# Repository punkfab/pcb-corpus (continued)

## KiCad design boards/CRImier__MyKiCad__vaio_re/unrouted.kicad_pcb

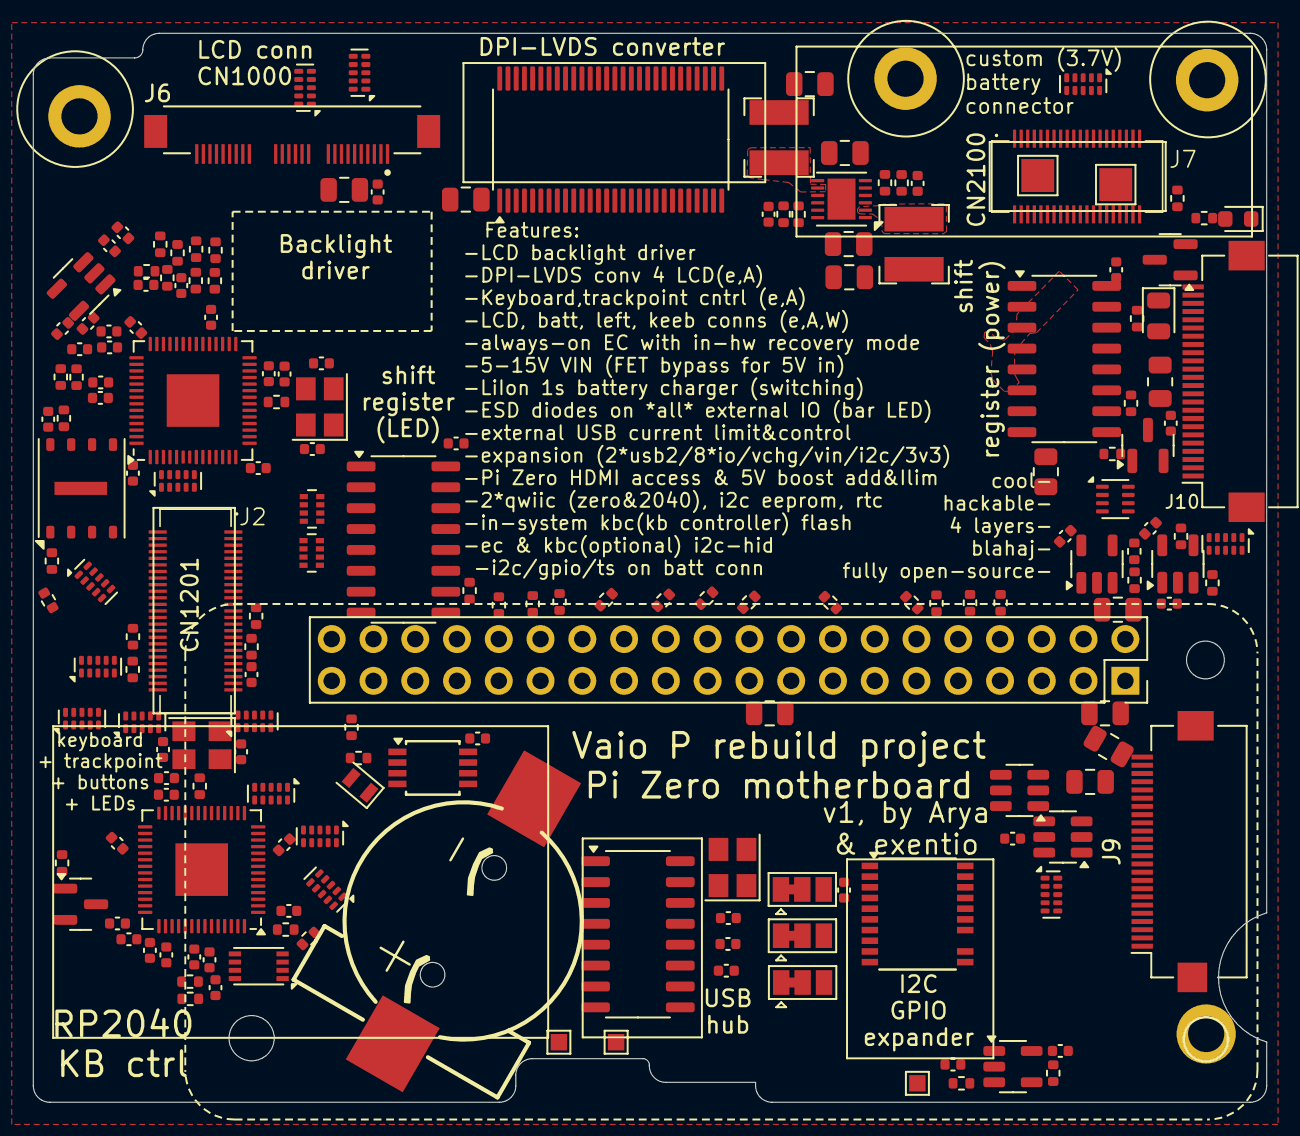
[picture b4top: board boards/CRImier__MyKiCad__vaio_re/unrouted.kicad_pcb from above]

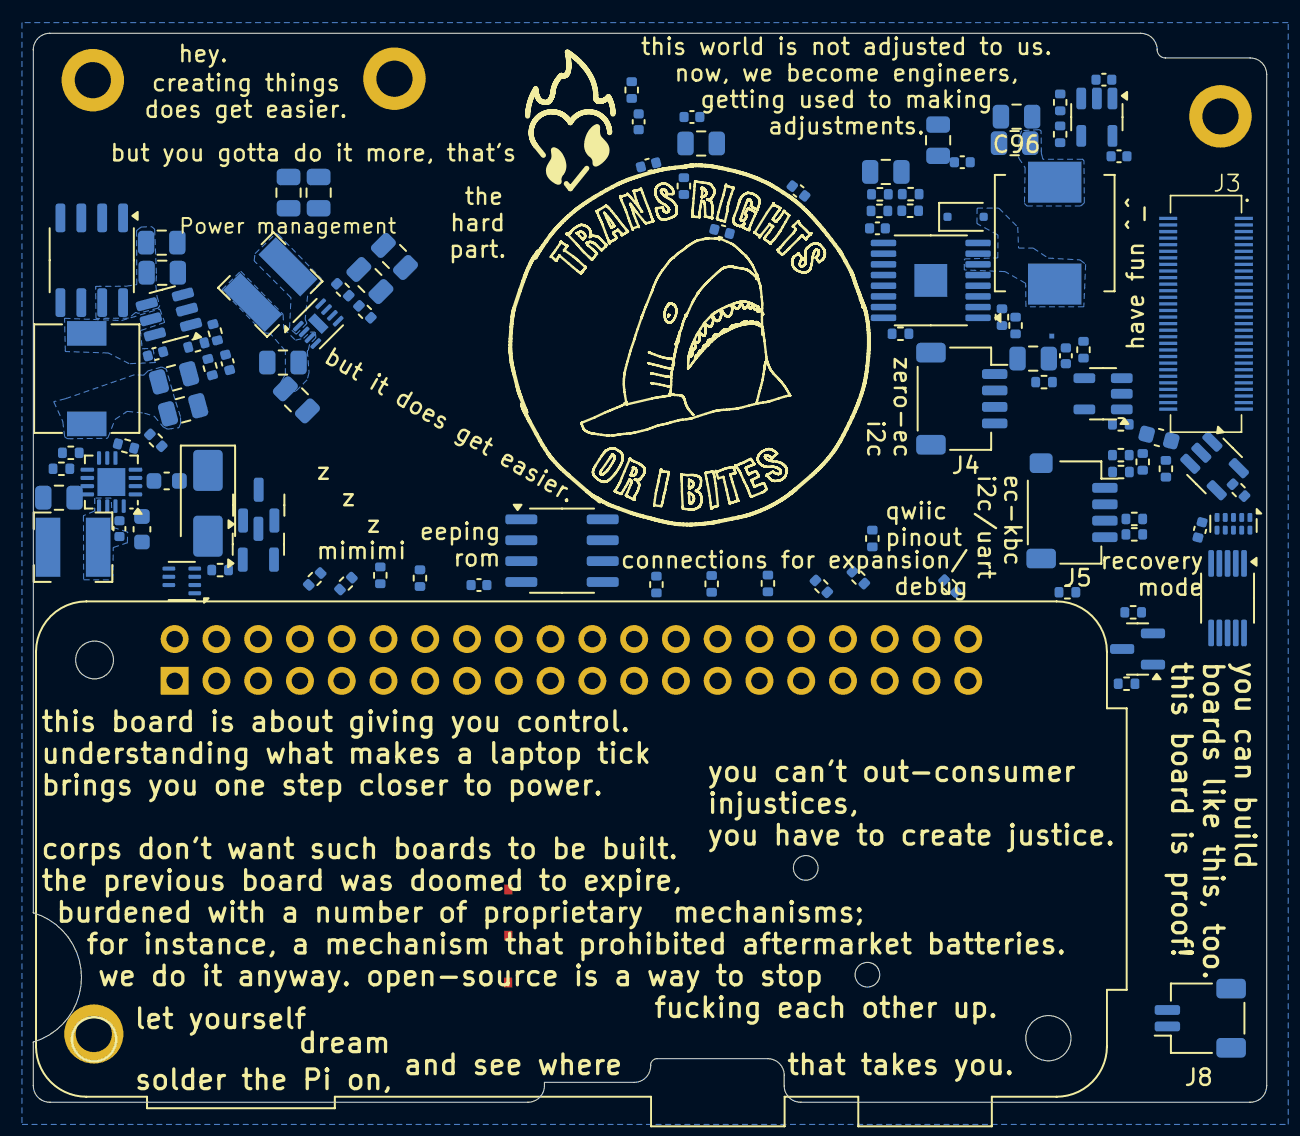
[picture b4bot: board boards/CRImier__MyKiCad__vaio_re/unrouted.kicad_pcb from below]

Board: 4 copper layers, 75.0 x 65.0 mm, 289 parts (106 on the bottom side), 267 nets, no tracks yet.

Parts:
BT1: Battery; BAT-SMD_CR1220-2ZX
C1, C2: 4.7uF; C_0805_2012Metric
C3, C4, C48, C49: 1uF; C_0805_2012Metric
C5, C6: 0.1uF; C_0402_1005Metric
C7, C8: 0.01uF; C_0402_1005Metric
C9, C10, C50, C51, C52, C53, C54, C55, C56, C57, C62, C90: 4u7; C_0805_2012Metric
C11, C12, C58: 100p; C_0402_1005Metric
C13, C14: 10u; C_0805_2012Metric
C15, C16, C17, C18, C19, C20, C21, C22, C24, C25, C26, C27, C28, C30, C33, C34, C35, C36, C37, C38, C40, C41, C42, C43, C44, C59, C60, C64, C65, C66, C67, C69, C70, C71, C72, C73, C74, C76, C91, C92, C93: 100nF; C_0402_1005Metric
C23, C29, C39, C45, C63, C75, C78, C79, C80, C82, C83, C84, C85, C86: 1uF; C_0402_1005Metric
C31, C32, C46, C47: 15pF; C_0402_1005Metric
C61, C88, C89: 4u7; C_0603_1608Metric
C68, C77, C87, C94, C95, C96, C97, C98: 22uF; C_0805_2012Metric
C81: 47nF; C_0402_1005Metric
D1: PMEG6010CEJ; D_SOD-323F
D2: SS34; D_SMA
D3: 5V1; D_0805_2012Metric
D4: LED_Small; LED_0603_1608Metric
H1, H2, H3, H4: MountingHole; MountingHole_2.2mm_M2_DIN965_Pad
IC1: SN75LVDS83B; TSSOP-56_6.1x14mm_P0.5mm
ISET1, ISET2, ISET3, ISET4: x; R_0402_1005Metric
J1: RPi_GPIO; Raspberry_Pi_Zero_Socketed_THT_FaceDown_MountingHoles
J2: AXK750147G_VAIO-P
J3: AXK760347G_VAIO-P
J4: qwiic; JST_SH_SM04B-SRSS-TB_1x04-1MP_P1.00mm_Horizontal
J5: qwiic?; JST_SH_SM04B-SRSS-TB_1x04-1MP_P1.00mm_Horizontal
J6: 20374-R30E-31; I-PEX_20374-R30E-31
J7: AXK740347G_VAIO-P; AXK750147G_VAIO-P
J8: RTC_BATT; JST_SH_SM02B-SRSS-TB_1x02-1MP_P1.00mm_Horizontal
J9, J10: EXP; Hirose_FH12-24S-0.5SH_1x24-1MP_P0.50mm_Horizontal
JP1: A0; SolderJumper-3_P1.3mm_Bridged12_Pad1.0x1.5mm
JP2: A1; SolderJumper-3_P1.3mm_Bridged12_Pad1.0x1.5mm
JP3: A2; SolderJumper-3_P1.3mm_Bridged12_Pad1.0x1.5mm
L1, L2: 4u7; L_Murata_23S4R7C
L3: DR73-470-R 47uH; L_Coilcraft_XAL6020-XXX
L4, L6: 1u; L_Murata_23S4R7C
L5: 4u7; L_6.3x6.3_H3
PD1, PD2, PD3, PD4, PD5, PD10: 10K; R_0402_1005Metric
PD6: RISET; R_0402_1005Metric
PD7, PD8, PD9: RVSET; R_0402_1005Metric
Q1, Q2, Q5, Q7: 2N7002; SOT-23
Q3, Q4: Q_PMOS_GSD; SOT-23
Q11: SI4909; SO-8_3.9x4.9mm_P1.27mm
R1, R2, R51, R54, R56: 470K; R_0402_1005Metric
R3, R4, R9, R10, R11, R12, R17, R18, R19, R34, R35, R42, R43, R50, R65: 4.7K; R_0402_1005Metric
R5, R6, R53, R55, R57, R58: 100K; R_0402_1005Metric
R7, R8, R13, R14, R32, R33, R40, R41, R60, R61: 27; R_0402_1005Metric
R15, R16: 1.8K; R_0402_1005Metric
R20, R21, R22, R23, R24, R25, R26, R27, R28, R29, R30, R31, R62, R63: R; R_0402_1005Metric
R36, R37, R38, R39: Pu; R_0402_1005Metric
R44: 5V_FB1; R_0402_1005Metric
R45: 5V_FB2; R_0402_1005Metric
R46: DC_FBU; R_0402_1005Metric
R47: DC_FBD; R_0402_1005Metric
R48: 5.1K; R_0402_1005Metric
R49: 5K1; R_0402_1005Metric
R52: 1K8; R_0805_2012Metric
R59: 1K8; R_0402_1005Metric
R64: 0R; R_0805_2012Metric
R66, R67, R68, R69, R70, R71, R72, R73, R74, R75, R76, R77, R78, R79, R80, R81, R82, R83, R84, R85, R86, R87: 47R; R_0402_1005Metric
RN1, RN2: 1.8K; R_Array_Concave_4x0402
TP1, TP2: TestPoint; TestPoint_Pad_2.0x2.0mm
TP3: TestPoint; TestPoint_Pad_1.0x1.0mm
TP4: D+; TestPoint_Pad_1.0x1.0mm
TP5: D-; TestPoint_Pad_1.0x1.0mm
TP6: HDMI_POWER; TestPoint_Pad_1.0x1.0mm
U1: AP2112K-3.3; SOT-23-5
U2: PAM2306AYPAA; WDFN-12-1EP_3x3mm_P0.45mm_EP1.7x2.5mm
U3: SL2.1A; SO-16_3.9x9.9mm_P1.27mm
U4, U6: RP2040; QFN-56-1EP_7x7mm_P0.4mm_EP3.2x3.2mm
U5: W25Q128JVS; DFN-8-1EP_3x2mm_P0.5mm_EP1.3x1.5mm
U7: W25Q128JVS; WSON-8-1EP_6x5mm_P1.27mm_EP3.4x4mm
U8: FSUSB42MUX; MSOP-10_3x3mm_P0.5mm
U9, U14, U15, U36: SY6280; SOT-23-5
U10: MIC2876; DFN-8-1EP_2x2mm_P0.5mm_EP0.6x1.2mm
U11: HTSSOP-16-1EP_4.4x5mm_P0.65mm_EP3x3mm
U12, U13: 74HC595; SO-16_3.9x9.9mm_P1.27mm
U16: RT6255; TSOT-23-6
U17: PCF85363ATT; TSSOP-8_3x3mm_P0.65mm
U18, U19: LM66200; Texas_R-PUSON-N8_USON-8-1EP_1.6x2.1mm_P0.5mm_EP0.4x1.7mm
U20: 24LC00; SOIC-8_3.9x4.9mm_P1.27mm
U21, U35: ESD; SOT-23-6
U22, U23, U24, U25, U26, U27, U31, U33, U34, U37, U39, U40, U41, U42, U43: TPD4E02B04DQA; USON-10_2.5x1.0mm_P0.5mm
U28: BQ2501x; QFN-16-1EP_3x3mm_P0.5mm_EP1.7x1.7mm
U29, U30: 74LVC1G17; SOT-23-5
U32: PCF8574ATS; SSOP-20_4.4x6.5mm_P0.65mm
Y1: 12MHz; Crystal_SMD_3225-4Pin_3.2x2.5mm
Y2, Y3: ABM8-272-T3; Crystal_SMD_3225-4Pin_3.2x2.5mm
Y4: Crystal; Crystal_SMD_TXC_9HT11-2Pin_2.0x1.2mm

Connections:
5VA_DET: R30.1, R31.2, U6.31 (GPIO20)
5V_EXT_EN: PD1.1, U6.32 (GPIO21), U9.4 (EN)
2040_G25: J7.21 (BATT1_PRS#), U6.37 (GPIO25), U37.1 (IO1), U37.10 (NC)
2040_G26: J7.18 (BATT_ID), U6.38 (GPIO26_ADC0), U37.4 (IO3), U37.7 (NC)
+1V1: C19.1, C21.1, C23.1, U4.23 (DVDD), U4.45 (VREG_VOUT), U4.50 (DVDD)
+1V1E: C35.1, C37.1, C39.1, U6.23 (DVDD), U6.45 (VREG_VOUT), U6.50 (DVDD)
+2V5: C2.1, C4.1, C6.1, C8.1, C13.1, J6.4, J6.5, J6.6, L1.2, R1.2
+3.3VP: C14.1, C97.1, J9.17, J9.18, L2.2, R2.2
+3V3: C1.1, C3.1, C5.1, C7.1, C15.1, C16.1, C18.1, C20.1, C22.1, C24.1, C25.1, C26.1, C27.1, C28.1, C29.1, C30.1, C67.1, C68.1, C69.1, C70.1, C71.1, C72.1, C73.1, C74.1, C75.1, C77.1, C78.1, IC1.1 (IOVCC@1), IC1.9 (VCC@1), IC1.26 (IOVCC@2), IC1.34 (PLLVCC), IC1.44 (LVDSVCC), J1.1 (3.3V), J1.17 (3.3V), J2.41 (+3VRUN), J5.2, J9.16, J10.9, JP1.1 (A), JP2.1 (A), JP3.1 (A), R3.2, R4.2, R9.2, R10.1, R36.1, R37.1, R38.1, R39.1, R50.2, U3.11 (VDD5), U3.13 (VDD33), U4.1 (IOVDD), U4.10 (IOVDD), U4.22 (IOVDD), U4.33 (IOVDD), U4.42 (IOVDD), U4.43 (ADC_AVDD), U4.44 (VREG_IN), U4.48 (USB_VDD), U4.49 (IOVDD), U5.8 (VCC), U11.9 (VIN), U17.8 (VDD), U20.1 (A0), U20.2 (A1), U20.3 (A2), U20.8 (VCC), U21.5 (VBUS), U32.5 (VDD), U35.5 (VBUS)
+3V3E: C33.1, C34.1, C36.1, C38.1, C40.1, C41.1, C42.1, C43.1, C44.1, C45.1, C61.2, C62.2, C66.1, C76.1, C91.1, C92.1, J2.43 (+3VALW), J4.2, R35.1, R42.2, R43.1, R51.2, R54.2, R56.2, R57.2, R62.2, R65.1, U1.5 (VOUT), U6.1 (IOVDD), U6.10 (IOVDD), U6.22 (IOVDD), U6.33 (IOVDD), U6.42 (IOVDD), U6.43 (ADC_AVDD), U6.44 (VREG_IN), U6.48 (USB_VDD), U6.49 (IOVDD), U7.8 (VCC), U8.1 (VCC), U12.16 (VCC), U13.16 (VCC), U29.5 (VCC), U30.5 (VCC)
+5VA: C85.1, J3.6 (+5VALW), J3.8 (+5VALW), J3.10 (+5VALW), J3.12 (+5VALW), R30.2, U9.1 (OUT)
+5VD: C52.1, C53.1, C79.1, C83.1, C86.1, J3.47 (USB_P0_5V), J3.49 (USB_P0_5V), J3.51 (USB_P0_5V), J3.53 (USB_P0_5V), J3.55 (USB_P0_5V), PD5.2, R44.2, U9.5 (IN), U10.8 (OUT), U15.5 (IN), U36.5 (IN)
+BATT: C90.1, J7.1 (+VBATT1), J7.2 (+VBATT1), J7.3 (+VBATT1), J7.4 (+VBATT1), J7.5 (+VBATT1), J7.6 (+VBATT1), J7.7 (+VBATT1), J7.8 (+VBATT1), J7.9 (+VBATT1), J7.10 (+VBATT1), J7.11 (+VBATT1), J7.12 (+VBATT1), J7.13 (+VBATT1), J7.14 (+VBATT1), J7.15 (+VBATT1), J7.16 (+VBATT1), J7.17 (+VBATT1), L4.2, Q3.2 (S), Q4.2 (S), TP2.1, U18.6 (VIN2), U19.6 (VIN2), U28.10 (BAT)
+VDC: C54.1, C56.1, D3.1 (K), J3.13 (=DC_IN_CHK), J3.15 (+VDC_IN), J3.17 (+VDC_IN), J3.19 (+VDC_IN), J3.21 (+VDC_IN), J3.23 (+VDC_IN), J3.25 (+VDC_IN), J3.27 (+VDC_IN), J3.29 (+VDC_IN), J3.31 (+VDC_IN), J3.33 (+VDC_IN), J10.19, J10.20, J10.21, J10.22, J10.23, J10.24, Q11.7 (D), Q11.8 (G), R26.2, R59.1, U16.4 (VIN)
/5V_FB: R44.1, R45.2, U10.5 (FB)
/5V_INT: C84.1, C98.1, J9.21, J9.22, J9.23, J9.24, U15.1 (OUT)
/5V_SW: L6.2, U10.1 (SW)
/5V_VIN: C55.1, C57.1, C58.1, D2.2 (A), L5.2, PD4.1, PD10.1, Q3.1 (G), Q4.1 (G), Q11.5 (D), Q11.6 (G), R46.2, U18.3 (VIN1), U19.3 (VIN1), U28.1 (VBUS)
/+VDC_G: D3.2 (A), Q11.2 (G), Q11.4 (G), R52.1, R59.2
/BAT_TS: J7.22 (SYS_PRS#), PD8.1, PD9.2, U28.7 (TS)
/CHG_REGN: C89.1, PD9.1, U28.2 (REGN)
/DC_FB: R48.1, U16.1 (FB)
/EC_BOOT: R17.1, U30.4
/EN_2V5: U2.6 (EN1), U13.3 (QD)
/EN_3V3: U2.12 (EN2), U13.1 (QB)
/EN_5V: U10.6 (EN), U13.2 (QC)
/EN_5VI: PD3.1, U13.6 (QG), U15.4 (EN)
/EN_CHG: U13.4 (QE), U28.6 (~EN)
/EN_DC: Q5.3 (D), R65.2, U16.2 (EN)
/EN_DC_INV: Q5.1 (G), U13.15 (QA)
/EN_ZERO: PD2.1, U13.7 (QH), U14.4 (EN)
/EUSB0_N: J9.10, U3.1 (DM4), U21.4 (I/O2)
/EUSB0_P: J9.9, U3.2 (DP4), U21.6 (I/O1)
/EUSB1_N: J9.12, U3.3 (DM3), U21.3 (I/O2)
/EUSB1_P: J9.11, U3.4 (DP3), U21.1 (I/O1)
/HDMI_POWER: C80.1, TP6.1, U36.1 (OUT)
/KB_RX: J5.4, R32.1, R36.2, R61.2
/KB_TX: J5.3, R33.1, R37.2, R60.1
/LED_CAPS_PRE: R15.1, R61.1, U4.16 (GPIO13)
/LED_NUM_PRE: R16.1, R60.2, U4.15 (GPIO12), U39.4 (IO3), U39.7 (NC)
/LX1: L1.1, U2.8 (LX1)
/LX2: L2.1, U2.2 (LX2)
/SW_CHG: C81.2, L4.1, U28.13 (SW), U28.14 (SW)
/SW_DC: C59.2, L5.1, U16.5 (LX)
/UH_1V8: C17.1, U3.14 (VDD18)
/USBIN_N: TP5.1, U3.9 (DM)
/USBIN_P: TP4.1, U3.10 (DP)
/USBh_DN: U3.7 (DM1), U8.6 (HSD1-)
/USBh_DP: U3.8 (DP1), U8.7 (HSD1+)
/USBi_DN: J3.5 (USB_P0-), U8.4 (D-), U31.1 (IO1), U31.10 (NC)
/USBi_DP: J3.7 (USB_P0+), U8.3 (D+), U31.2 (IO2), U31.9 (NC)
/USBk_DN: R8.2, U3.5 (DM2)
/USBk_DP: R7.2, U3.6 (DP2)
/USBp_DN: R14.2, U8.8 (HSD2-)
/USBp_DP: R13.2, U8.9 (HSD2+)
/VDC_BYPASS: Q7.1 (G), R49.1, U13.5 (QF)
/VIN: C9.1, C10.1, C49.1, C63.1, C82.1, C93.1, C94.1, C95.1, C96.1, D2.1 (K), L3.1, Q3.3 (D), Q4.3 (D), R28.2, R64.2, U1.1 (VIN), U1.3 (EN), U2.1 (VIN2), U2.7 (VIN1), U14.5 (IN), U19.2 (OUT), U19.7 (OUT)
/VIN_PI: C87.1, J1.2 (5V), J1.4 (5V), U14.1 (OUT)
/eUSB_OE: R58.1, U6.34 (GPIO22), U8.10 (~OE)
/eUSB_SEL: R57.1, U6.35 (GPIO23), U8.2 (SEL)
ADC2: C64.1, R26.1, R27.2, U6.39 (GPIO27_ADC1)
ADC3: R62.1, R63.2, U6.40 (GPIO28_ADC2)
ADC4: C65.1, R28.1, R29.2, U6.41 (GPIO29_ADC3)
B0: IC1.15 (D15), R78.2
B1: IC1.19 (D18), R84.2
B2: IC1.20 (D19), R85.2
B3: IC1.22 (D20), R71.2
B4: IC1.23 (D21), R72.2
B5: IC1.24 (D22), R81.2
CLKIN: IC1.31 (CLKIN), R83.2
CLKSEL: IC1.17 (CLKSEL), R3.1
COL0: J2.6 (KSO<6>), U4.39 (GPIO27_ADC1), U23.4 (IO3), U23.7 (NC)
COL1: J2.7 (KSO<7>), U4.5 (GPIO3), U27.5 (IO4), U27.6 (NC)
COL2: J2.15 (KSI<3>), U4.9 (GPIO7), U26.5 (IO4), U26.6 (NC)
COL3: J2.17 (KSO<9>), U4.11 (GPIO8), U22.1 (IO1), U22.10 (NC)
COL4: J2.18 (KSO<10>), U4.32 (GPIO21), U25.1 (IO1), U25.10 (NC)
COL5: J2.20 (KSO<11>), U4.31 (GPIO20), U25.2 (IO2), U25.9 (NC)
COL6: J2.19 (KSO<12>), U4.12 (GPIO9), U22.2 (IO2), U22.9 (NC)
COL7: J2.5 (KSO<5>), U4.4 (GPIO2), U27.4 (IO3), U27.7 (NC)
COL8: J2.4 (KSO<2>), U4.40 (GPIO28_ADC2), U23.2 (IO2), U23.9 (NC)
COL9: J2.23 (KSO<13>), U4.14 (GPIO11), U22.5 (IO4), U22.6 (NC), U39.5 (IO4), U39.6 (NC)
COL10: J2.22 (KSO<14>), U4.30 (GPIO19), U25.4 (IO3), U25.7 (NC)
COL11: J2.21 (KSO<15>), U4.13 (GPIO10), U22.4 (IO3), U22.7 (NC)
COL12: J2.3 (KSO<3>), U4.3 (GPIO1), U27.2 (IO2), U27.9 (NC)
COL13: J2.2 (KSO<4>), U4.41 (GPIO29_ADC3), U23.1 (IO1), U23.10 (NC)
COL14: J2.24 (KSO<0>), U4.29 (GPIO18), U25.5 (IO4), U25.6 (NC)
COL15: J2.1 (KSO<1>), U4.2 (GPIO0), U27.1 (IO1), U27.10 (NC)
EC_RUN: C60.2, R51.1, U6.26 (RUN)
ENABLE: IC1.30 (D26), R70.2
G0: IC1.4 (D7), R80.2
G1: IC1.6 (D8), R82.2
G2: IC1.7 (D9), R69.2
G3: IC1.11 (D12), R86.2
G4: IC1.12 (D13), R75.2
G5: IC1.14 (D14), R74.2
G18: TP3.1, U6.29 (GPIO18)
GND: BT1.2 (-), C1.2, C2.2, C3.2, C4.2, C5.2, C6.2, C7.2, C8.2, C9.2, C10.2, C11.2, C12.2, C13.2, C14.2, C15.2, C16.2, C17.2, C18.2, C19.2, C20.2, C21.2, C22.2, C23.2, C24.2, C25.2, C26.2, C27.2, C28.2, C29.2, C30.2, C31.2, C32.2, C33.2, C34.2, C35.2, C36.2, C37.2, C38.2, C39.2, C40.2, C41.2, C42.2, C43.2, C44.2, C45.2, C46.2, C47.2, C48.2, C49.2, C50.2, C51.2, C52.2, C53.2, C54.2, C55.2, C56.2, C57.2, C63.2, C64.2, C65.2, C66.2, C67.2, C68.2, C69.2, C70.2, C71.2, C72.2, C73.2, C74.2, C75.2, C76.2, C77.2, C78.2, C79.2, C80.2, C82.2, C83.2, C84.2, C85.2, C86.2, C87.2, C88.2, C89.2, C90.2, C91.2, C92.2, C93.2, C94.2, C95.2, C96.2, C97.2, C98.2, H1.1, H2.1, H3.1, H4.1, IC1.2 (D5), IC1.5 (GND@1), IC1.8 (D10), IC1.10 (D11), IC1.13 (GND@2), IC1.16 (D16), IC1.18 (D17), IC1.21 (GND@3), IC1.25 (D23), IC1.29 (GND@4), IC1.33 (GND@5), IC1.35 (GND@6), IC1.36 (GND@7), IC1.43 (GND@8), IC1.49 (GND@9), IC1.50 (D27), IC1.53 (GND@10), ISET1.2, ISET2.2, ISET3.2, ISET4.2, J1.6 (GND), J1.9 (GND), J1.14 (GND), J1.20 (GND), J1.25 (GND), J1.30 (GND), J1.34 (GND), J1.39 (GND), J2.39 (GND), J2.45 (GND), J2.46 (GND), J2.47 (GND), J2.48 (GND), J2.49 (GND), J2.50 (GND), J3.1 (GND), J3.2 (GND), J3.3 (GND), J3.4 (GND), J3.9 (GND), J3.11 (GND), J3.14 (GND), J3.16 (GND), J3.20 (GND), J3.22 (GND), J3.26 (GND), J3.32 (GND), J3.35 (GND), J3.37 (GND), J3.39 (GND), J3.41 (GND), J3.43 (GND), J3.44 (GND), J3.45 (GND), J3.48 (GND), J3.52 (GND), J3.57 (GND), J3.59 (GND), J3.60 (GND), J4.1, J4.MP (MountPin), J5.1, J5.MP (MountPin), J6.7, J6.8, J6.9, J6.S1 (SHIELD), J6.S2 (SHIELD__1), J7.23 (BATT_RTN), J7.24 (BATT_RTN), J7.25 (BATT_RTN), J7.26 (BATT_RTN), J7.27 (BATT_RTN), J7.28 (BATT_RTN), J7.29 (BATT_RTN), J7.30 (BATT_RTN), J7.31 (BATT_RTN), J7.32 (BATT_RTN), J7.33 (BATT_RTN), J7.34 (BATT_RTN), J7.35 (BATT_RTN), J7.36 (BATT_RTN), J7.37 (BATT_RTN), J7.38 (BATT_RTN), J7.39 (BATT_RTN), J7.40 (BATT_RTN), J8.2, J8.MP (MountPin), J9.1, J9.2, J9.3, J9.4, J9.19, J9.20, J9.MP (MountPin), J10.1, J10.2, J10.3, J10.4, J10.5, J10.6, J10.7, J10.8, J10.MP (MountPin), JP1.3 (B), JP2.3 (B), JP3.3 (B), PD1.2, PD2.2, PD3.2, PD4.2, PD6.2, PD7.2, PD8.2, Q1.2 (S), Q2.2 (S), Q5.2 (S), Q7.3 (D), R5.2, R6.2, R19.2, R20.1, R23.1, R25.1, R27.1, R29.1, R31.1, R34.2, R45.1, R47.1, R49.2, R58.2, R63.1, TP1.1, U1.2 (GND), U2.3 (GND), U2.9 (GND), U2.13 (GND), U3.12 (GND), U4.19 (TESTEN), U4.57 (GND), U5.4 (GND), U6.19 (TESTEN), U6.57 (GND), U7.4 (GND), U7.9 (GND), U8.5 (GND), U9.2 (GND), U10.2 (PGND), U10.4 (AGND), U10.7 (PG), U10.9 (EP_GND), U11.2 (GND), U11.4 (PGND), U11.17 (GND), U12.8 (GND), U13.8 (GND), U13.13 (~OE), U14.2 (GND), U15.2 (GND), U16.3 (GND), U17.4 (VSS), U18.1 (GND), U18.4 (ON#), U18.5 (GND), U19.1 (GND), U19.4 (ON#), U19.5 (GND), U20.4 (GND), U20.7 (WP), U21.2 (GND), U22.3 (G), U22.8 (G), U23.3 (G), U23.8 (G), U24.3 (G), U24.8 (G), U25.3 (G), U25.8 (G), U26.3 (G), U26.8 (G), U27.3 (G), U27.8 (G), U28.11 (GND), U28.12 (GND), U28.17 (GND), U29.3 (GND), U30.3 (GND), U31.3 (G), U31.8 (G), U32.15 (VSS), U33.3 (G), U33.8 (G), U34.3 (G), U34.8 (G), U35.2 (GND), U36.2 (GND), U37.3 (G), U37.8 (G), U39.3 (G), U39.8 (G), U40.3 (G), U40.8 (G), U41.3 (G), U41.8 (G), U42.3 (G), U42.8 (G), U43.3 (G), U43.4 (IO3), U43.7 (NC), U43.8 (G), Y1.2, Y1.4, Y2.2, Y2.4, Y3.2, Y3.4
GP22: J1.15 (BCM22), U6.14 (GPIO11)
GP25: J1.22 (BCM25), J9.15, U32.1 (~INT), U35.4 (I/O2)
GP26: J1.37 (BCM26), U6.16 (GPIO13)
GP27: J1.13 (BCM27), J10.13, U34.5 (IO4), U34.6 (NC)
GPE_P0: J10.16, U32.10 (P0), U34.1 (IO1), U34.10 (NC)
GPE_P1: J10.15, U32.11 (P1), U34.2 (IO2), U34.9 (NC)
GPE_P2: J10.14, U32.12 (P2), U34.4 (IO3), U34.7 (NC)
GPE_P3: D4.1 (K), U28.3 (STAT), U32.14 (P3), U35.3 (I/O2)
GPE_P4: J9.5, U32.16 (P4), U33.5 (IO4), U33.6 (NC)
GPE_P5: J9.6, U32.17 (P5), U33.4 (IO3), U33.7 (NC)
GPE_P6: J9.7, U32.19 (P6), U33.2 (IO2), U33.9 (NC)
GPE_P7: J9.8, U32.20 (P7), U33.1 (IO1), U33.10 (NC)
HSYNC: IC1.27 (D24), R77.2
IO_A0: JP1.2 (C), U32.6 (A0)
IO_A1: JP2.2 (C), U32.7 (A1)
IO_A2: JP3.2 (C), U32.9 (A2)
KB_BOOT: R41.2, U6.2 (GPIO0)
KB_RUN: U4.26 (RUN), U6.13 (GPIO10)
LCD_INS: J6.30, U6.36 (GPIO24)
LED_CAPS: J2.26 (LED_CAPS), R15.2, RN1.1 (R1.1)
LED_CHG: J2.44 (LED_CHG), RN1.4 (R4.1)
LED_DISK: J2.40 (LED_PATA), RN1.2 (R2.1)
LED_NUM: J2.27 (LED_NUM), R16.2, RN2.3 (R3.1)
LED_PWM: R40.2, U6.15 (GPIO12)
LED_PWR: J2.42 (LED_PWR), RN1.3 (R3.1)
LED_RTN: J2.33 (LED_RTN), Q1.3 (D)
LED_SCRL: J2.25 (LED_SCRL), RN2.4 (R4.1)
LED_STBY: J2.35 (LED_STBY), RN2.1 (R1.1)
LED_WIFI: J2.31 (LED_WIRELESS), RN2.2 (R2.1)
L_CTRL: R21.2, U11.10 (CTRL)
L_FAULT: U6.27 (GPIO16), U11.3 (FAULT)
L_FB: R20.2, R21.1, U11.5 (FB)
L_PWM: U6.28 (GPIO17), U11.7 (EN/PWM)
L_SW: D1.2 (A), L3.2, U11.6 (SW)
L_VFMAX: R22.1, R23.2, U11.12 (VFMAX)
L_VFMIN: R24.1, R25.2, U11.11 (VFMIN)
unnamed: C32.1, R12.1, Y2.3
unnamed: C47.1, R18.1, Y3.3
unnamed: C58.2, R46.1, R47.2, R48.2
unnamed: C60.1, U29.4
unnamed: C61.1, R53.2, R54.1, U30.2
unnamed: C62.1, R55.2, R56.1, U29.2
unnamed: D4.2 (A), PD10.2
unnamed: J1.27 (BCM0_ID_SD), R83.1
unnamed: J1.28 (BCM1_ID_SC), R70.1
unnamed: J1.3 (BCM2_SDA), R76.1
unnamed: J1.5 (BCM3_SCL), R77.1
unnamed: J1.7 (BCM4_GPCLK0), R78.1
unnamed: J1.29 (BCM5), R84.1
unnamed: J1.31 (BCM6), R85.1
unnamed: J1.26 (BCM7_CE1), R71.1
unnamed: J1.24 (BCM8_CE0), R72.1
unnamed: J1.21 (BCM9_MISO), R81.1
unnamed: J1.19 (BCM10_MOSI), R80.1
unnamed: J1.23 (BCM11_SCLK), R82.1
unnamed: J1.32 (BCM12_PWM0), R69.1
unnamed: J1.33 (BCM13_PWM1), R86.1
unnamed: J1.8 (BCM14_TXD), R75.1
unnamed: J1.10 (BCM15_RXD), R74.1
unnamed: J1.36 (BCM16), R68.1
unnamed: J1.11 (BCM17), R79.1
unnamed: J1.12 (BCM18_PCM_C), R73.1
unnamed: J1.35 (BCM19_MISO_PCM_FS), R87.1
unnamed: J1.38 (BCM20_MOSI_PCM_DI), R67.1
unnamed: J1.40 (BCM21_SCLK_PCM_DO), R66.1
unnamed: Q1.1 (G), R40.1
unnamed: Q2.3 (D), R11.1
unnamed: Q2.1 (G), R41.1
unnamed: Q7.2 (S), R52.2
unnamed: Q11.1 (S), Q11.3 (S)
unnamed: RN1.8 (R1.2), U12.1 (QB)
unnamed: RN1.7 (R2.2), U12.2 (QC)
unnamed: RN1.6 (R3.2), U12.3 (QD)
unnamed: RN1.5 (R4.2), U12.15 (QA)
unnamed: RN2.8 (R1.2), U12.4 (QE)
unnamed: RN2.7 (R2.2), U12.5 (QF)
unnamed: RN2.6 (R3.2), U12.6 (QG)
unnamed: RN2.5 (R4.2), U12.7 (QH)
unnamed: C11.1, R1.1, R5.1, U2.4 (FB1)
unnamed: C12.1, R2.1, R6.1, U2.10 (FB2)
unnamed: U3.16 (XIN), Y1.3
unnamed: U3.15 (XOUT), Y1.1
unnamed: R8.1, U4.46 (USB_DM)
unnamed: R7.1, U4.47 (USB_DP)
unnamed: R33.2, U6.6 (GPIO4)
unnamed: R32.2, U6.7 (GPIO5)
unnamed: R14.1, U6.46 (USB_DM)
unnamed: R13.1, U6.47 (USB_DP)
unnamed: ISET1.1, U9.3 (ISET)
unnamed: R19.1, U11.13 (RSET)
unnamed: ISET2.1, U14.3 (ISET)
unnamed: ISET3.1, U15.3 (ISET)
unnamed: C59.1, U16.6 (BOOT)
unnamed: U17.1 (OSCI), Y4.2
unnamed: U17.2 (OSCO), Y4.1
unnamed: C81.1, U28.15 (BTST)
unnamed: PD6.1, U28.4 (ICHG)
unnamed: C88.1, U28.16 (PMID)
unnamed: PD7.1, U28.9 (VSET)
unnamed: U31.4 (IO3), U31.7 (NC)
unnamed: U31.5 (IO4), U31.6 (NC)
unnamed: PD5.1, U36.4 (EN)
unnamed: ISET4.1, U36.3 (ISET)
unnamed: U42.4 (IO3), U42.7 (NC)
unnamed: U42.5 (IO4), U42.6 (NC)
PS2_CLK: J2.29 (SP_CLK), R10.2, U4.28 (GPIO17), U42.2 (IO2), U42.9 (NC)
PS2_DAT: J2.28 (SP_DAT), R9.1, U4.27 (GPIO16), U42.1 (IO1), U42.10 (NC)
QSPI_E_SCLK: U6.52 (QSPI_SCLK), U7.6 (CLK)
QSPI_E_SD0: U6.53 (QSPI_SD0), U7.5 (DI(IO0))
QSPI_E_SD1: U6.55 (QSPI_SD1), U7.2 (DO(IO1))
QSPI_E_SD2: U6.54 (QSPI_SD2), U7.3 (IO2)
QSPI_E_SD3: U6.51 (QSPI_SD3), U7.7 (IO3)
QSPI_E_SS: R17.2, R42.1, U6.56 (QSPI_SS), U7.1 (~CS)
QSPI_SCLK: U4.52 (QSPI_SCLK), U5.6 (CLK)
QSPI_SD0: U4.53 (QSPI_SD0), U5.5 (DI(IO0))
QSPI_SD1: U4.55 (QSPI_SD1), U5.2 (DO(IO1))
QSPI_SD2: U4.54 (QSPI_SD2), U5.3 (IO2)
QSPI_SD3: U4.51 (QSPI_SD3), U5.7 (IO3)
QSPI_SS: R11.2, R50.1, U4.56 (QSPI_SS), U5.1 (~CS)
R0: IC1.51 (D0), R68.2
R1: IC1.52 (D1), R79.2
R2: IC1.54 (D2), R73.2
R3: IC1.55 (D3), R87.2
R4: IC1.56 (D4), R67.2
R5: IC1.3 (D6), R66.2
ROW0: J2.12 (KSI<2>), U4.36 (GPIO24), U24.2 (IO2), U24.9 (NC)
ROW1: J2.16 (KSO<8>), U4.34 (GPIO22), U24.5 (IO4), U24.6 (NC)
ROW2: J2.11 (KSI<1>), U4.7 (GPIO5), U26.2 (IO2), U26.9 (NC)
ROW3: J2.13 (KSI<0>), U4.8 (GPIO6), U26.4 (IO3), U26.7 (NC)
ROW4: J2.14 (KSI<4>), U4.35 (GPIO23), U24.4 (IO3), U24.7 (NC)
ROW5: J2.9 (KSI<5>), U4.6 (GPIO4), U26.1 (IO1), U26.10 (NC)
ROW6: J2.8 (KSI<6>), U4.38 (GPIO26_ADC0), U23.5 (IO4), U23.6 (NC)
ROW7: J2.10 (KSI<7>), U4.37 (GPIO25), U24.1 (IO1), U24.10 (NC)
RTC_BATT: BT1.1 (+), J8.1, U17.3 (VBAT)
RTC_INT: U6.12 (GPIO9), U17.7 (~INTA)
RX0+: IC1.47 (Y0P), J6.28, U41.4 (IO3), U41.7 (NC)
RX0-: IC1.48 (Y0M), J6.29, U41.5 (IO4), U41.6 (NC)
RX1+: IC1.45 (Y1P), J6.26, U41.1 (IO1), U41.10 (NC)
RX1-: IC1.46 (Y1M), J6.27, U41.2 (IO2), U41.9 (NC)
RX2+: IC1.41 (Y2P), J6.24, U40.4 (IO3), U40.7 (NC)
RX2-: IC1.42 (Y2M), J6.25, U40.5 (IO4), U40.6 (NC)
RXCLK+: IC1.39 (CLCKOUTP), J6.22, U40.1 (IO1), U40.10 (NC)
RXCLK-: IC1.40 (CLCKOUTM), J6.23, U40.2 (IO2), U40.9 (NC)
SCL: J1.18 (BCM24), J4.4, J7.20 (SMB_0CLK), J9.14, J10.18, R39.2, U6.18 (GPIO15), U17.6 (SCL), U20.6 (SCL), U32.2 (SCL), U35.6 (I/O1), U37.5 (IO4), U37.6 (NC)
SDA: J1.16 (BCM23), J4.3, J7.19 (SMB_0DATA), J9.13, J10.17, R38.2, U6.17 (GPIO14), U17.5 (SDA), U20.5 (SDA), U32.4 (SDA), U35.1 (I/O1), U37.2 (IO2), U37.9 (NC)
SH2_RST: R43.2, U13.10 (~SRCLR)
SHTDN: IC1.32 (~SHTDN), R4.1, U6.30 (GPIO19)
SH_CLK: J10.11, U6.8 (GPIO6), U12.11 (SRCLK), U13.11 (SRCLK)
SH_DIN: U6.9 (GPIO7), U12.14 (SER)
SH_DOUT1: U12.9 (QH'), U13.14 (SER)
SH_DOUT2: J10.10, U13.9 (QH')
SH_LATCH: J10.12, U6.11 (GPIO8), U12.12 (RCLK), U13.12 (RCLK)
SH_OE: R34.1, U12.13 (~OE)
SH_RST: R35.2, U12.10 (~SRCLR)
SW_LID: J2.32 (SW_LID#), U6.3 (GPIO1), U43.1 (IO1), U43.10 (NC)
SW_PWR: J2.34 (SW_PWR#), R55.1, U6.4 (GPIO2), U43.2 (IO2), U43.9 (NC)
SW_SP0: J2.36 (SW_SP0#), U4.18 (GPIO15), U39.1 (IO1), U39.10 (NC)
SW_SP1: J2.37 (SW_SP1#), U4.17 (GPIO14), U39.2 (IO2), U39.9 (NC)
SW_WIFI: J2.38 (SW_RADIO_DIS), R53.1, U6.5 (GPIO3), U43.5 (IO4), U43.6 (NC)
VAD: C48.1, D1.1 (K), J6.1, J6.2, R22.2, R24.2
VCD1: J6.18, U11.1 (LED1)
VCD2: J6.17, U11.16 (LED2)
VCD3: J6.16, U11.15 (LED3)
VCD4: J6.15, U11.14 (LED4)
VIN_5VREG: C50.1, C51.1, L6.1, R64.1, U10.3 (VIN), U18.2 (OUT), U18.7 (OUT)
VSYNC: IC1.28 (D25), R76.2
XIN: C31.1, U4.20 (XIN), Y2.1
XIN_E: C46.1, U6.20 (XIN), Y3.1
XOUT: R12.2, U4.21 (XOUT)
XOUT_E: R18.2, U6.21 (XOUT)

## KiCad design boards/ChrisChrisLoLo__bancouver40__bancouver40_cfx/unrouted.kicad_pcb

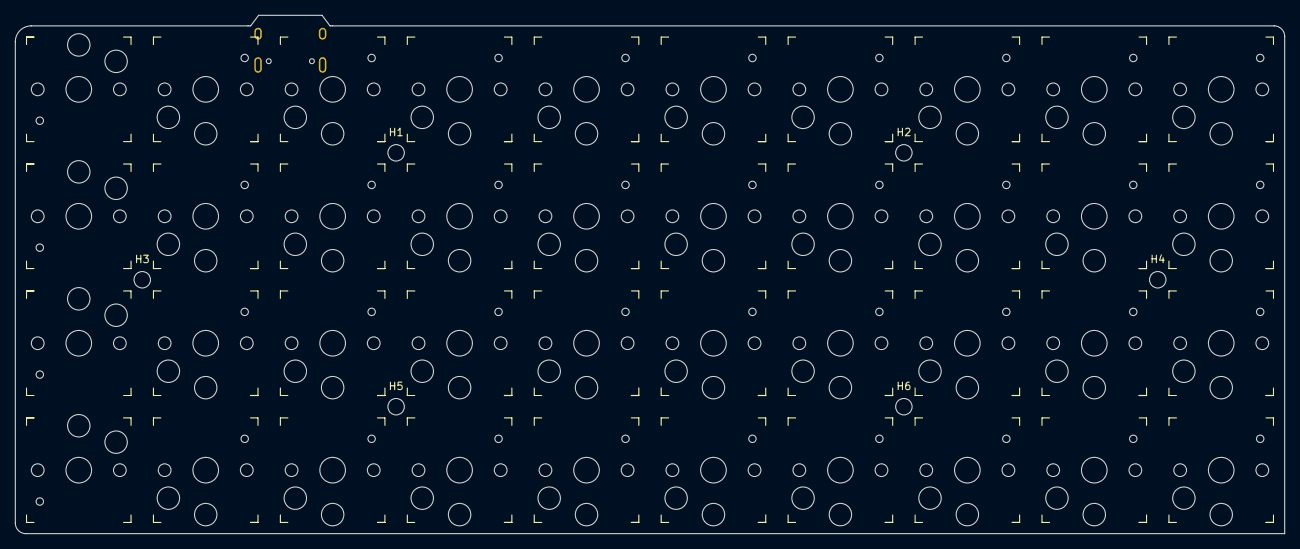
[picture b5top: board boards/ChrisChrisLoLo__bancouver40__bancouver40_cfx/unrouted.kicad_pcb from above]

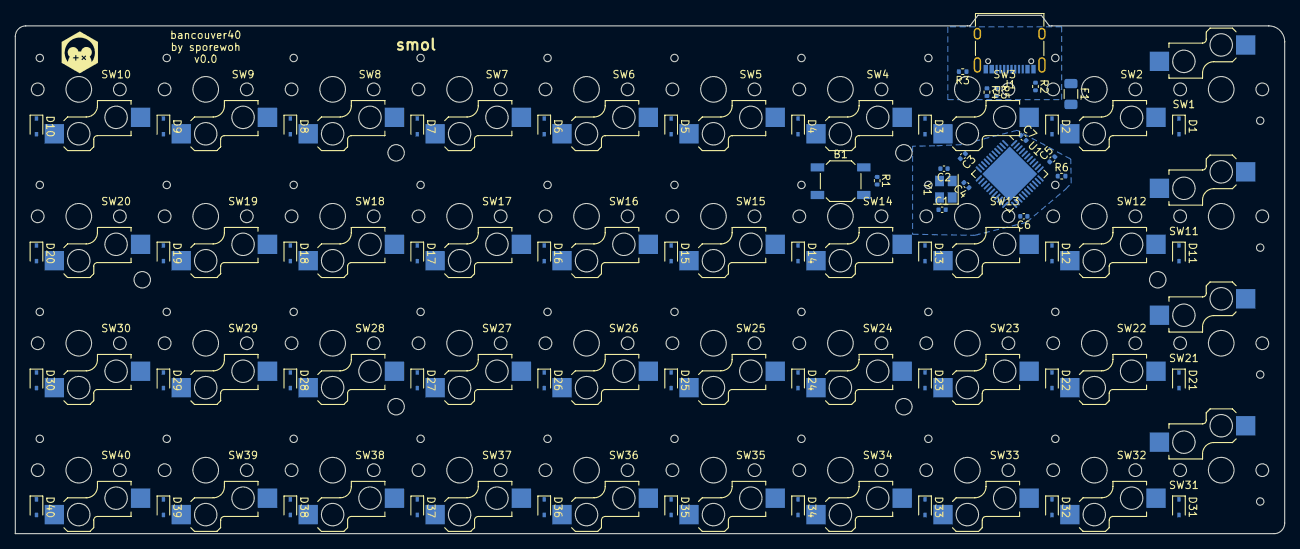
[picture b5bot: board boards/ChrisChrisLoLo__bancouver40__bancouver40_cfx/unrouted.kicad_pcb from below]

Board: 2 copper layers, 170.0 x 69.4 mm, 104 parts (58 on the bottom side), 68 nets, no tracks yet.

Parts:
B1: SW_Push; SW_SPST_SKQG_WithoutStem
C1, C2: 22pF; C_0402_1005Metric
C3: 1uF; C_0402_1005Metric
C4, C5, C6: 0.1uF; C_0402_1005Metric
C7: 10uF; C_0402_1005Metric
D1, D2, D3, D4, D5, D6, D7, D8, D9, D10, D11, D12, D13, D14, D15, D16, D17, D18, D19, D20, D21, D22, D23, D24, D25, D26, D27, D28, D29, D30, D31, D32, D33, D34, D35, D36, D37, D38, D39, D40: D_Small; D_SOD-323
F1: 500mA; Fuse_1206_3216Metric
H1, H2, H3, H4, H5, H6: MountingHole; MountingHole_2.2mm_M2_ISO7380
J1: USB_C_Receptacle_USB2.0; USB_C_Receptacle_XKB_U262-16XN-4BVC11
R1, R6: 10k; R_0402_1005Metric
R2, R3: 5k1; R_0402_1005Metric
R4, R5: 22; R_0402_1005Metric
SW1, SW2, SW3, SW4, SW5, SW6, SW7, SW8, SW9, SW10, SW11, SW12, SW13, SW14, SW15, SW16, SW17, SW18, SW19, SW20, SW21, SW22, SW23, SW24, SW25, SW26, SW27, SW28, SW29, SW30, SW31, SW32, SW33, SW34, SW35, SW36, SW37, SW38, SW39, SW40: SW_Push; Kailh_socket_PG1350
U1: ATmega32U4-M; QFN-44-1EP_7x7mm_P0.5mm_EP5.2x5.2mm
Y1: 16MHz; Crystal_SMD_3225-4Pin_3.2x2.5mm

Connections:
+5V: C4.1, C5.1, C6.1, C7.1, F1.2, R1.1, U1.2 (UVCC), U1.7 (VBUS), U1.14 (VCC), U1.24 (AVCC), U1.34 (VCC), U1.44 (AVCC)
D+: J1.A6 (D+), J1.B6 (D+), R4.1
D-: J1.A7 (D-), J1.B7 (D-), R5.1
D_res+: R4.2, U1.4 (D+)
D_res-: R5.2, U1.3 (D-)
GND: B1.1, C1.1, C2.1, C3.2, C4.2, C5.2, C6.2, C7.2, J1.A1 (GND), J1.A12 (GND), J1.B1 (GND), J1.B12 (GND), J1.S1 (SHIELD), R2.2, R3.2, R6.2, U1.5 (UGND), U1.15 (GND), U1.23 (GND), U1.35 (GND), U1.43 (GND), U1.45 (GND), Y1.2, Y1.4
unnamed: B1.2, R1.2, U1.13 (~RESET)
unnamed: C1.2, U1.17 (XTAL1), Y1.1
unnamed: C2.2, U1.16 (XTAL2), Y1.3
unnamed: C3.1, U1.6 (UCAP)
unnamed: D1.2 (A), SW1.1
unnamed: D2.2 (A), SW2.1
unnamed: D3.2 (A), SW3.1
unnamed: D4.2 (A), SW4.1
unnamed: D5.2 (A), SW5.1
unnamed: D6.2 (A), SW6.1
unnamed: D7.2 (A), SW7.1
unnamed: D8.2 (A), SW8.1
unnamed: D9.2 (A), SW9.1
unnamed: D10.2 (A), SW10.1
unnamed: D11.2 (A), SW11.1
unnamed: D12.2 (A), SW12.1
unnamed: D13.2 (A), SW13.1
unnamed: D14.2 (A), SW14.1
unnamed: D15.2 (A), SW15.1
unnamed: D16.2 (A), SW16.1
unnamed: D17.2 (A), SW17.1
unnamed: D18.2 (A), SW18.1
unnamed: D19.2 (A), SW19.1
unnamed: D20.2 (A), SW20.1
unnamed: D21.2 (A), SW21.1
unnamed: D22.2 (A), SW22.1
unnamed: D23.2 (A), SW23.1
unnamed: D24.2 (A), SW24.1
unnamed: D25.2 (A), SW25.1
unnamed: D26.2 (A), SW26.1
unnamed: D27.2 (A), SW27.1
unnamed: D28.2 (A), SW28.1
unnamed: D29.2 (A), SW29.1
unnamed: D30.2 (A), SW30.1
unnamed: D31.2 (A), SW31.1
unnamed: D32.2 (A), SW32.1
unnamed: D33.2 (A), SW33.1
unnamed: D34.2 (A), SW34.1
unnamed: D35.2 (A), SW35.1
unnamed: D36.2 (A), SW36.1
unnamed: D37.2 (A), SW37.1
unnamed: D38.2 (A), SW38.1
unnamed: D39.2 (A), SW39.1
unnamed: D40.2 (A), SW40.1
unnamed: J1.A5 (CC1), R2.1
unnamed: J1.B5 (CC2), R3.1
unnamed: R6.1, U1.33 (~HWB/PE2)
VBUS: F1.1, J1.A4 (VBUS), J1.A9 (VBUS), J1.B4 (VBUS), J1.B9 (VBUS)
col1: SW1.2, SW11.2, SW21.2, SW31.2, U1.29 (PB5)
col2: SW2.2, SW12.2, SW22.2, SW32.2, U1.28 (PB4)
col3: SW3.2, SW13.2, SW23.2, SW33.2, U1.27 (PD7)
col4: SW4.2, SW14.2, SW24.2, SW34.2, U1.26 (PD6)
col5: SW5.2, SW15.2, SW25.2, SW35.2, U1.25 (PD4)
col6: SW6.2, SW16.2, SW26.2, SW36.2, U1.22 (PD5)
col7: SW7.2, SW17.2, SW27.2, SW37.2, U1.21 (PD3)
col8: SW8.2, SW18.2, SW28.2, SW38.2, U1.20 (PD2)
col9: SW9.2, SW19.2, SW29.2, SW39.2, U1.19 (PD1)
col10: SW10.2, SW20.2, SW30.2, SW40.2, U1.18 (PD0)
row1: D1.1 (K), D2.1 (K), D3.1 (K), D4.1 (K), D5.1 (K), D6.1 (K), D7.1 (K), D8.1 (K), D9.1 (K), D10.1 (K), U1.41 (PF0)
row2: D11.1 (K), D12.1 (K), D13.1 (K), D14.1 (K), D15.1 (K), D16.1 (K), D17.1 (K), D18.1 (K), D19.1 (K), D20.1 (K), U1.40 (PF1)
row3: D21.1 (K), D22.1 (K), D23.1 (K), D24.1 (K), D25.1 (K), D26.1 (K), D27.1 (K), D28.1 (K), D29.1 (K), D30.1 (K), U1.39 (PF4)
row4: D31.1 (K), D32.1 (K), D33.1 (K), D34.1 (K), D35.1 (K), D36.1 (K), D37.1 (K), D38.1 (K), D39.1 (K), D40.1 (K), U1.38 (PF5)
